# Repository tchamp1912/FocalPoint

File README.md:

# FocalPoint

FocalPoint is the attention router for your coding agents. It keeps Claude
Code, Codex CLI, and Cursor sessions visible in one native macOS dashboard,
then takes you straight to the agent that needs you next.

<p align="center"><em>One glance for every agent. One hotkey to jump back into the loop.</em></p>

## One hotkey takes you to the agent that needs you next

FocalPoint prioritizes errors and input requests across **Cursor, Claude Code,
and Codex**, then brings the corresponding window, tab, or pane forward—no
hunting through terminals.

Run several agents in parallel without becoming their human task scheduler.
When one needs approval, clarification, or help recovering from an error,
FocalPoint moves it to the front of the queue. Press the attention hotkey—or
the matching key on the macropad—to land where the work is waiting. Press it
again to move to the next agent that needs you.

Meanwhile, the menu-bar dashboard and desktop widget keep the whole operation
visible: which agents are thinking, which are running tools, which are done,
and how much context and quota each one has left.

## Install

FocalPoint currently requires **macOS 14 or newer on Apple Silicon**.

Install the prerequisites:

```sh
xcode-select --install
brew install rust jq
```

For precise managed-session focus and input routing, tmux is an optional
dependency:

```sh
brew install tmux
```

Then clone and run the installer:

```sh
git clone https://github.com/tchamp1912/FocalPoint.git
cd FocalPoint
./install.sh
```

The installer shows everything it will change and asks for confirmation. To
skip that prompt, run `./install.sh --yes`.

It will:

- build and install the `focalpointd` daemon, general `focalpoint` CLI, narrow
  native `fpctl-agent` orchestration client, and `focalpoint-mcp` coordination
  server;
- install and launch the native FocalPoint menu-bar app;
- configure a launchd user service so the daemon starts automatically;
- install the guarded `focalpoint-orchestrator` agent-control skill;
- install the Claude Code, Codex CLI, and Cursor adapters;
- install the managed-session launcher under `~/.config/focalpoint/` while
  preserving any existing FocalPoint tmux configuration;
- merge FocalPoint lifecycle hooks into each installed agent's user config,
  backing up those files before changing them;
- register the identity-bound coordination MCP server with Claude, Codex, and
  Cursor without overwriting same-name configurations; and
- preserve an existing `~/.config/focalpoint/config.toml`.

The app also includes a curated workflow catalog. **Start Workflow** and
**Workflow Editor** list bundled formations separately from installed packages.
Installing one asks for confirmation, copies its referenced agent types too,
and refuses any name collision rather than overwriting an existing package.

Restart any agent sessions that were already open so they load the new hooks.
The FocalPoint keyboard icon will appear in the macOS menu bar. Waiting/error
sessions are highlighted in the desktop widget without system notifications.
An orchestrator can set the daemon's attention order with `fpctl-agent`; the
app and attention key follow that same daemon-owned order.

With optional tmux support installed, start a managed agent using
`~/.config/focalpoint/focalpoint-run.sh claude` (or replace `claude` with
`codex` or `gemini`). See [the orchestrator guide](orchestrator/) for checkout usage and
layout options.

### Try it without the hardware

The app and all agent integrations work without a physical macropad. Install
in mock-device mode to exercise the complete software stack:

```sh
./install.sh --mock
```

### Verify the installation

```sh
focalpoint sessions       # live sessions and their assigned slots
focalpoint get-state      # aggregate agent state
```

`focalpoint ping` additionally checks for a connected hardware device, so it
is expected to fail with an app-only install unless the daemon is in mock mode.

## Features

### Attention routing, not notification noise

- Prioritize sessions that need intervention: errors first, then approval or
  input requests.
- Jump to the corresponding Cursor workspace, Claude terminal tab, or Codex
  working surface for that session.
- Cycle forward or backward through the attention queue with configurable
  global hotkeys.
- Let an orchestrator agent replace that queue with an explicit
  session order; the attention keys follow it without moving numbered slots.
- Launch a specific Claude or Codex model for a literal task in an exact, already-prepared
  directory. Environment/worktree setup remains the orchestrator's job.
- Read bounded normalized transcript tails and gracefully stop only the
  managed sessions associated with matching orchestrator task IDs.
- Use the same flow from numbered session keys on the physical macropad.
- Keep working while background agents think and run tools; FocalPoint tells
  you where your attention has the highest value.
- Permission requests get a two-second grace period, so Claude/Codex
  auto-approvals do not create false attention signals; only a request that
  remains blocked reaches `approval`; ordinary input requests use `waiting`.

### Every agent in one place

- Track concurrent Claude Code, Codex CLI, and Cursor sessions.
- Keep numbered slots stable while sessions change state, then compact them
  after a session ends or is removed.
- See the model, working directory, session name, current state, and elapsed
  time at a glance.
- Rename, reorder, focus, or end sessions directly from the app.

### Live stats and context pressure

- Display input/output tokens, tool calls, turns, subagents, and cost whenever
  the provider exposes them.
- Watch context-window consumption on a compact per-session gauge.
- Choose which stat badges appear from Settings.
- Set token and cost budget alerts for visual warning states.

### Status that is hard to miss

FocalPoint normalizes agent lifecycle events into six states:

| State | Meaning |
|---|---|
| `idle` | No active work |
| `thinking` | The model is reasoning or generating |
| `running` | A tool or command is executing |
| `waiting` | The agent needs ordinary user input |
| `approval` | A Claude Code permission decision needs attention |
| `done` | The current turn completed |
| `error` | Something failed and needs attention |

Those states drive the menu-bar attention badge, desktop widget, optional
keyboard backlight, and the RGB pattern assigned to each physical key.

### Account usage monitoring

- View Claude short-window and weekly quota periods.
- Read Codex plan limits through the local Codex app-server integration.
- Track Cursor API and Auto usage from the local Cursor sign-in.
- See utilization percentages and reset times without leaving your workflow.

Usage monitoring stays local and can be enabled or disabled per integration.

### Native macOS controls

- Compact menu-bar dashboard with a waiting/approval/error attention badge.
- Movable translucent desktop widget with the same live session data.
- Configurable global hotkeys for focusing sessions, accepting/rejecting,
  starting tasks, push-to-talk, and jumping through the attention queue.
- Quick actions that run in a session's working directory.
- Local history for completed sessions.

### Customizable hardware feedback

- Set a color, pattern, and animation period for every state.
- Use physical session keys to jump directly to the matching agent.
- Map the remaining keys, rotary dial, and joystick to your preferred agent
  workflow.
- Run the same action path through hotkeys when hardware is not connected.

## Supported integrations

| Integration | Live states | Session stats | Context gauge | Account usage |
|---|---:|---:|---:|---:|
| Claude Code | Yes | Yes | Yes | Yes |
| Codex CLI | Yes | Yes | Yes | Yes |
| Cursor | Yes | Yes | When available | Yes |
| Custom scripts and tools | Yes | Whatever you report | Optional | Optional |

Provider APIs expose different information, so a missing badge means that the
current integration or event did not report that value—not that the session
failed to register.

## Configure

Open **FocalPoint → Settings** from the menu-bar dashboard to configure:

- the desktop widget and menu-bar appearance;
- visible stat badges, budget alerts, and context-window fallback;
- Claude, Codex, and Cursor account-usage monitors;
- global hotkeys and attention-navigation order;
- per-state colors and LED animation patterns; and
- session history.

Low-level daemon actions and hardware mappings live in:

```text
~/.config/focalpoint/config.toml
```

## Update or uninstall

Pull the latest version and rerun the idempotent installer:

```sh
git pull
./install.sh
```

On every update, the installer also prunes obsolete files that a previous
FocalPoint release recorded as managed, removes managed binary copies from an
inactive install prefix, replaces the agent skill as an exact source snapshot,
and removes a duplicate FocalPoint app from the inactive Applications folder.
User configuration, session history, logs, and unrelated files are preserved.

To preview or perform a clean uninstall:

```sh
./uninstall.sh --dry-run
./uninstall.sh
```

## Build your own integration

Any tool that can run a shell command can publish state:

```sh
focalpoint set-state running \
  --session my-session \
  --kind my-agent \
  --label "Implement login flow" \
  --cwd "$PWD"
```

Adapters can attach optional telemetry with repeated `--meta key=value`
arguments. See [the adapter guide](adapters/) for complete examples.

## Developer documentation

The public README intentionally focuses on installing and using FocalPoint.
Contributor and implementation details live in:

- [CLAUDE.md](CLAUDE.md) — repository guidance and component map
- [PLAN.md](PLAN.md) — product, hardware, and roadmap notes
- [PROTOCOL.md](PROTOCOL.md) — daemon, adapter, and device protocol
- [app/README.md](app/) — macOS app behavior and development
- [adapters/README.md](adapters/) — provider and custom adapter development

FocalPoint is in active development. The app and mock-device stack are usable
today; the open-hardware macropad is still evolving.

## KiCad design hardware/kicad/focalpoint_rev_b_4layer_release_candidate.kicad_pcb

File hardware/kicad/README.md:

# FocalPoint KiCad Rev B

This directory is the persistent KiCad 10 workspace. The verified schematic is
the hierarchical root `focalpoint.kicad_sch` and its three child sheets; the current PCB is
`focalpoint_rev_b_4layer_release_candidate.kicad_pcb`. It is a fully routed four-layer
prototype candidate. Native KiCad DRC reports zero errors and zero unconnected
pads and zero violations. Thirty-seven intentionally modified embedded
footprints are locked to `FocalPoint.pretty` and independently audited. It is
not orderable until an independent review, purchased-part enclosure fit check,
and JLCPCB upload review are completed.

## Schematic hierarchy

- `focalpoint_power.kicad_sch`: USB power entry, charging, battery monitoring,
  3.3 V conversion, 5 V boost, and LED-rail switching.
- `focalpoint_signals.kicad_sch`: nRF52840 module, USB data protection,
  programming/debug, reset, and signal-conditioning parts.
- `focalpoint_peripherals.kicad_sch`: 13 keys and RGB LEDs, encoder, joystick,
  and capacitive-touch input.

Cross-sheet connections retain their reviewed global net names. This makes the
design a navigable file hierarchy without changing the electrical graph. The
locked pre-refactor capture is `focalpoint_flat_reference.kicad_sch`; running
`hierarchize_schematic.py` regenerates the hierarchy from that reference.
The generator also replaces the original stretched placeholder bodies with
conventional resistor, capacitor, inductor, TVS, switch, battery, and
power-flag notation. Each A2 child sheet uses a checked fixed-cell layout;
`hierarchical_schematic_layout_validation.txt` records zero overlapping block
pairs and confirms that every block remains inside the printable area.

The production stack-up, internal-plane policy, routing classes, and mandatory
USB impedance confirmation are defined in [PCB_FABRICATION.md](PCB_FABRICATION.md).

## Refresh the mechanical foundation

```sh
npx --yes ergogen@4.1.0 hardware/ergogen -o hardware/ergogen/output
hardware/kicad/refresh-from-ergogen.sh
```

The refresh script refuses to overwrite a board that has already gained
KiCad-owned electrical work. Once schematic capture or manual placement starts,
move Ergogen changes across deliberately instead of replacing the board.

Open `focalpoint_rev_b_4layer_release_candidate.kicad_pro` and
`focalpoint_rev_b_4layer_release_candidate.kicad_pcb` in KiCad 10. The
active 116 mm square design presents 16 input positions in a 4×4 layout: 13
direct-scan MX hot-swap keys plus the top-left EC11 encoder, top-right analog
joystick, and bottom-right capacitive touch input. Every mechanical key has an
independently addressable RGB LED.

## Functional blocks

1. `keys`: 13 direct GPIO key inputs, hot-swap sockets, and no matrix diodes.
2. `controls`: EC11 A/B/push and the selected joystick X/Y/push.
3. `mcu`: certified nRF52840 module, SWD, reset, and boot/recovery.
4. `usb`: USB-C USB 2.0 device, CC resistors, ESD, and data protection.
5. `power`: protected 1-cell LiPo, charger with power-path management, battery
   measurement, 3.3 V regulation, and switched/current-budgeted LED rail.
6. `rgb`: 13 SK6812 MINI-E LEDs, local bypassing, data conditioning, and test
   pads.

Do not assign unverified footprints for the radio, charger, battery connector,
or USB-C receptacle from a generic name. Pin them to an orderable manufacturer
part and verify the land pattern against its current datasheet first.

## Release-candidate build

After refilling zones, running native DRC, and saving its zero-violation report:

```sh
python3 hardware/kicad/build_release_candidate.py \
  --drc-report hardware/kicad/focalpoint_rev_b_4layer_release_DRC.rpt
```

The output is `release_candidate_rev_b_4layer/` plus Rev B candidate ZIP
archives. Read `RELEASE_STATUS.txt`; the builder requires a report containing
zero DRC violations, zero unconnected pads, and zero footprint errors.

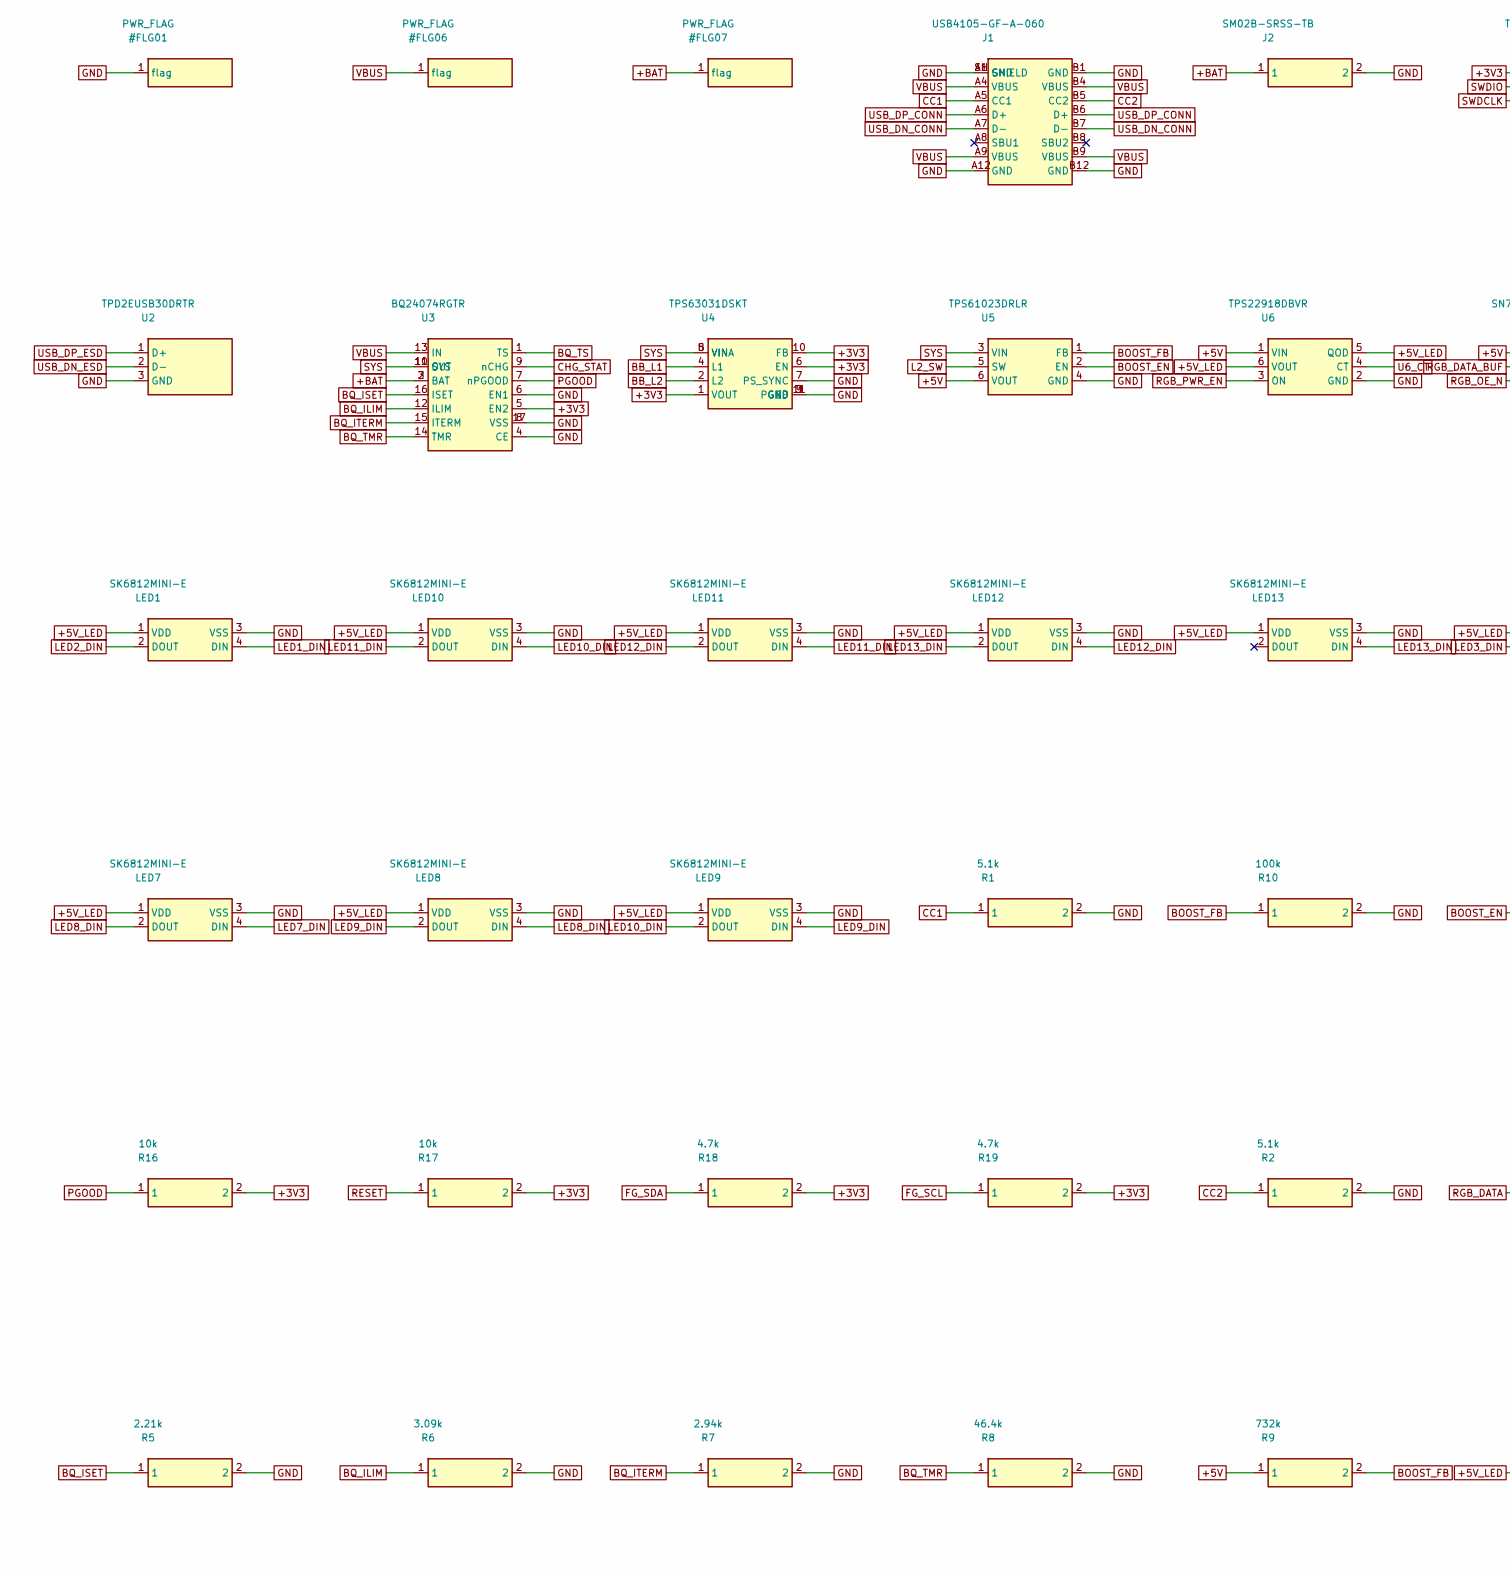
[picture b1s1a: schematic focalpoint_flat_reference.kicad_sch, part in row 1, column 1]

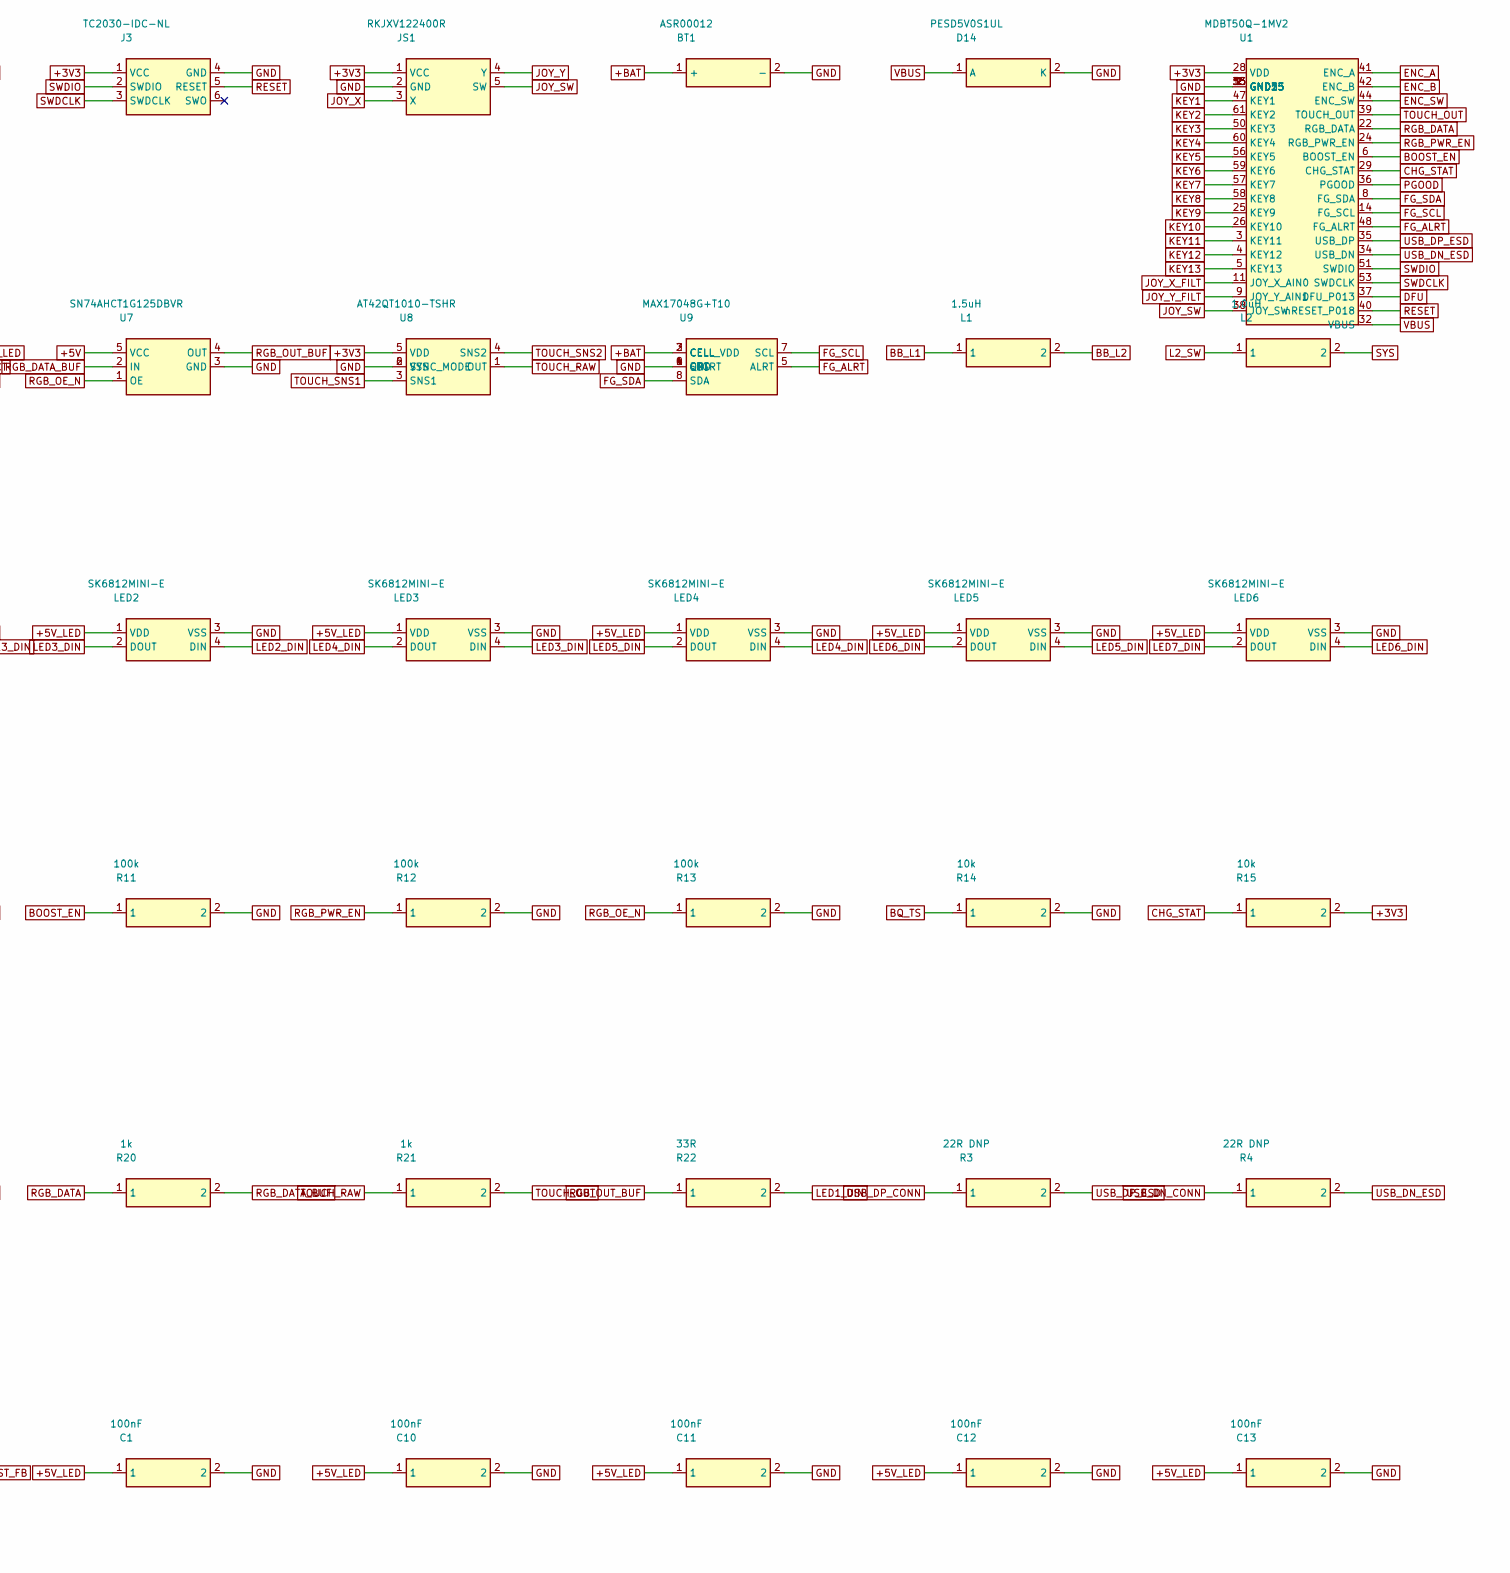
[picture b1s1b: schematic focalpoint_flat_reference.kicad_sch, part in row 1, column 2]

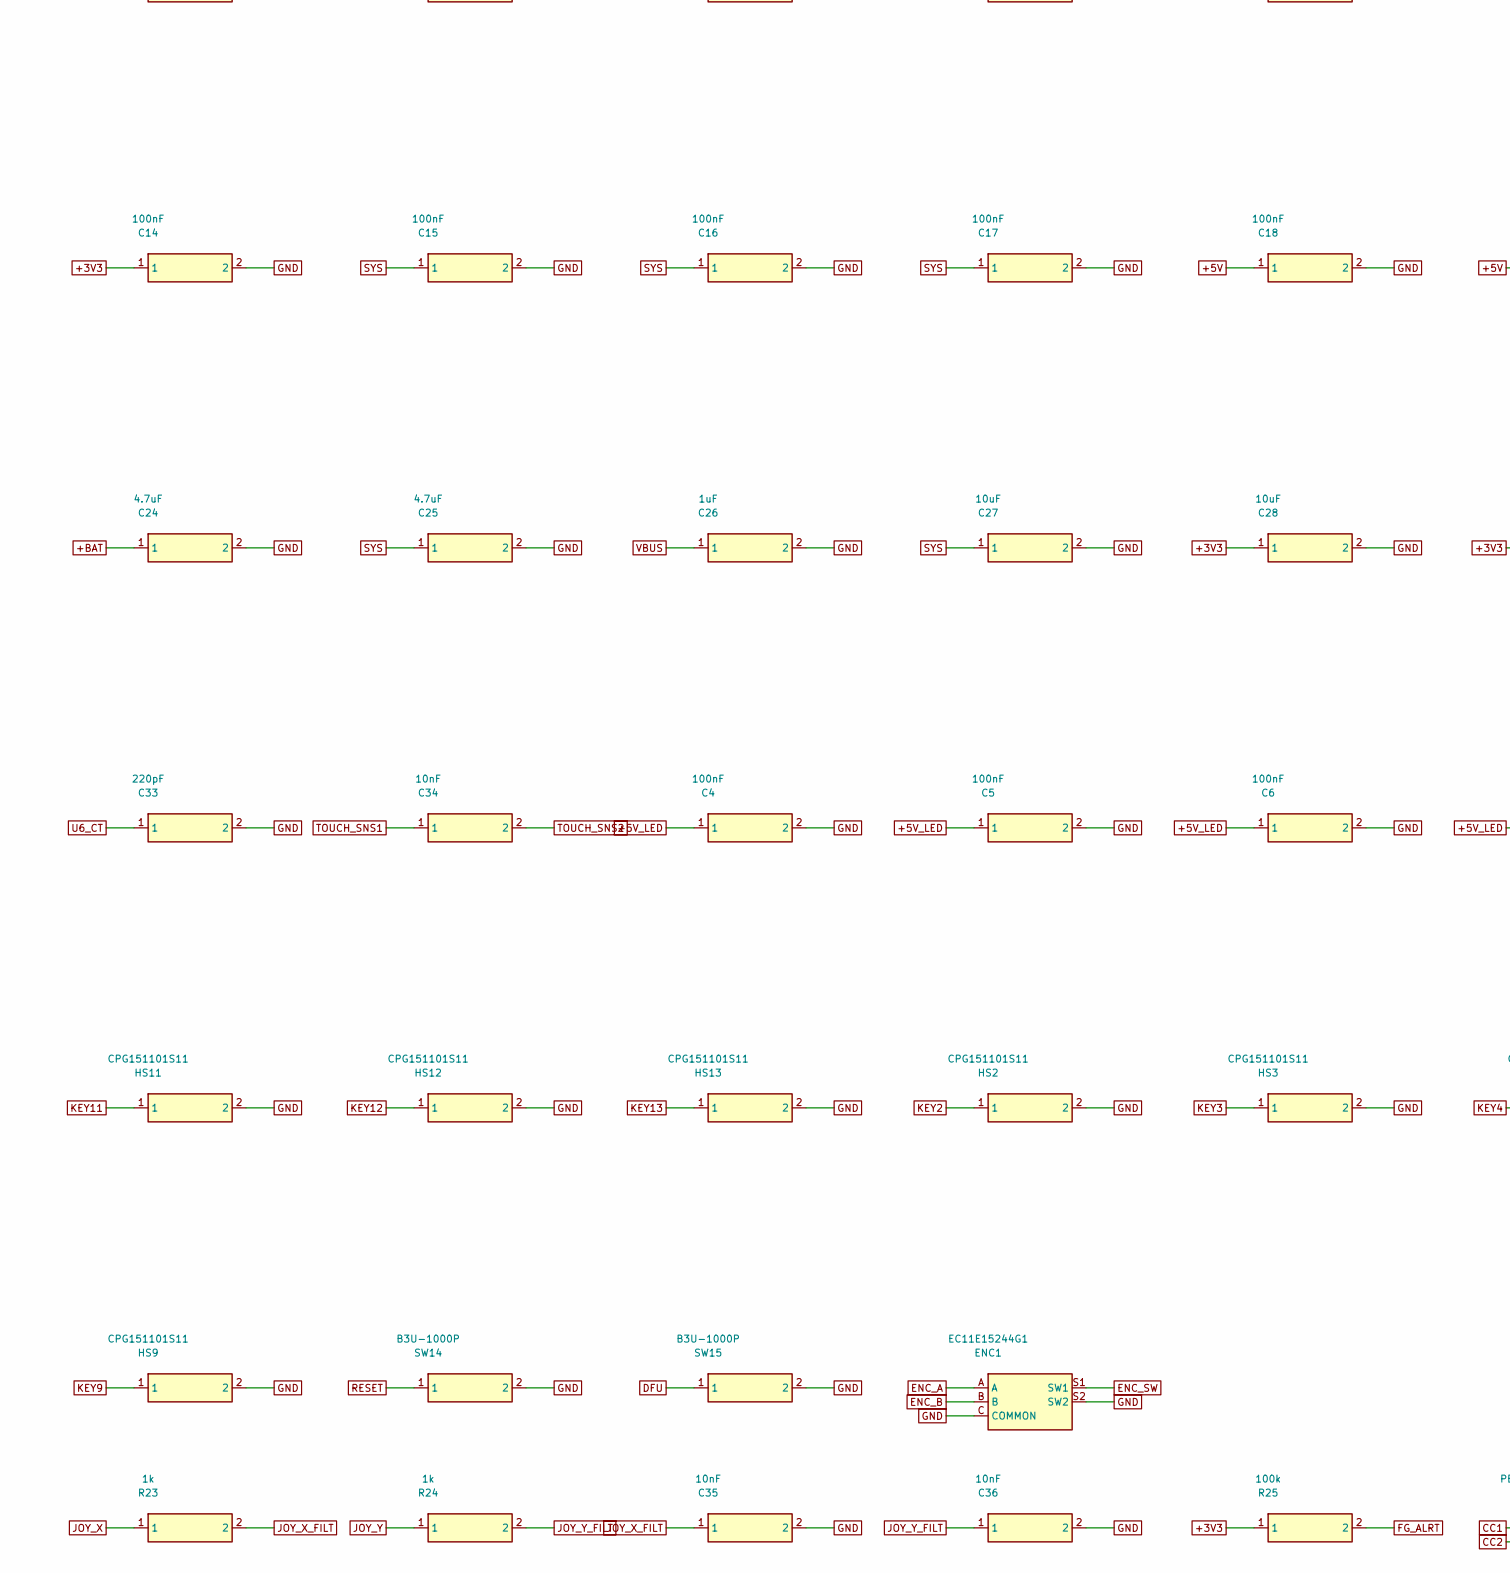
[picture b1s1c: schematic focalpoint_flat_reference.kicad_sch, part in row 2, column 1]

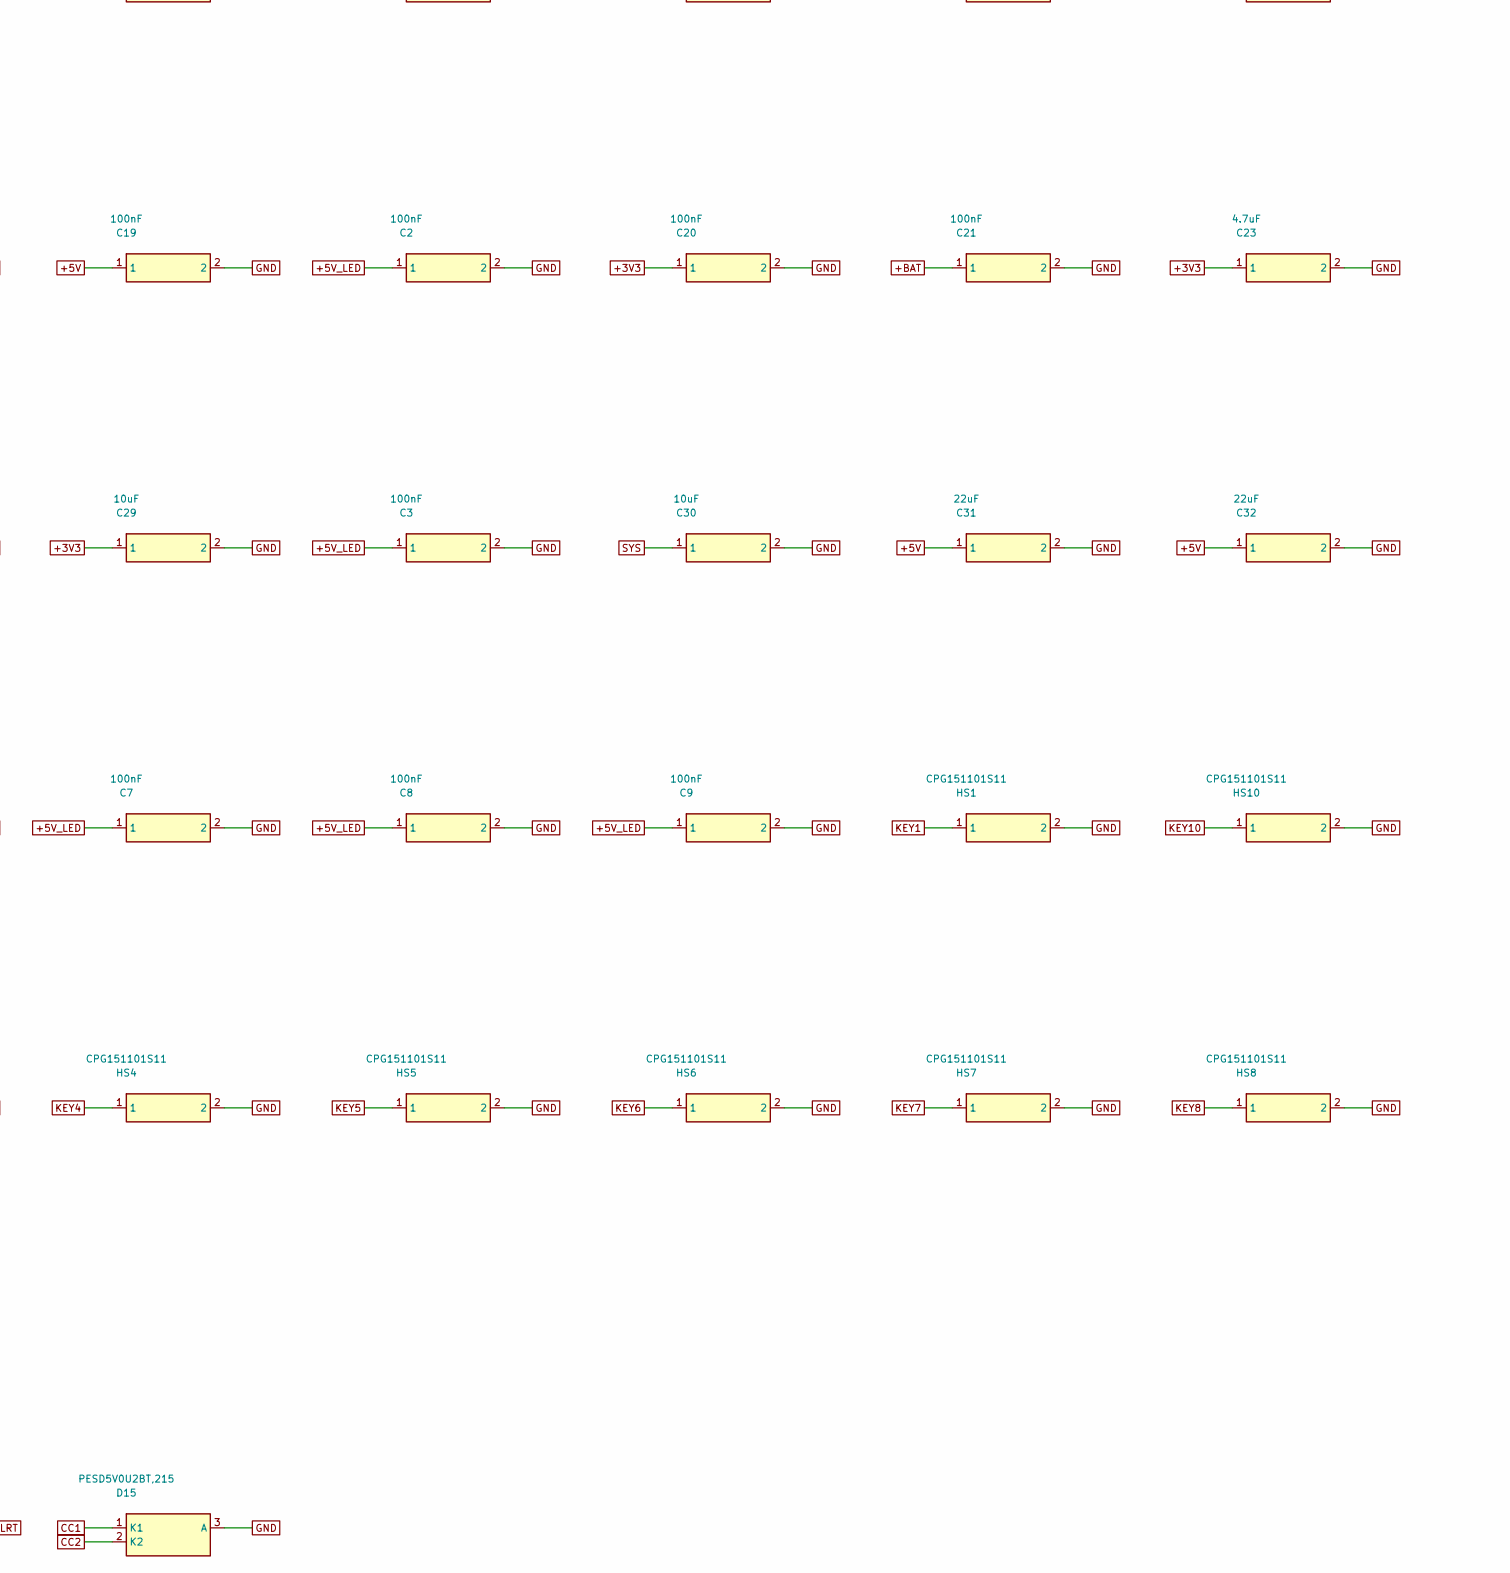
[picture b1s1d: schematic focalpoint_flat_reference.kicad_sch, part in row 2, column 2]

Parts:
BT1: ASR00012
C1, C2, C3, C4, C5, C6, C7, C8, C9, C10, C11, C12, C13, C14, C15, C16, C17, C18, C19, C20, C21: 100nF; C_0603_1608Metric
C23, C24, C25: 4.7uF; C_0603_1608Metric
C26: 1uF; C_0603_1608Metric
C27, C28, C29, C30: 10uF; C_0603_1608Metric
C31, C32: 22uF; C_0603_1608Metric
C33: 220pF; C_0603_1608Metric
C34, C35, C36: 10nF; C_0603_1608Metric
D14: PESD5V0S1UL; D_SOD-882
D15: PESD5V0U2BT,215; SOT-23
ENC1: EC11E15244G1; RotaryEncoder_Alps_EC11E-Switch_Vertical_H20mm
HS1, HS2, HS3, HS4, HS5, HS6, HS7, HS8, HS9, HS10, HS11, HS12, HS13: CPG151101S11; Kailh_CPG151101S11_Hotswap
J1: USB4105-GF-A-060; USB_C_Receptacle_GCT_USB4105-xx-A_16P_TopMnt_Horizontal
J2: SM02B-SRSS-TB; JST_SH_SM02B-SRSS-TB_1x02-1MP_P1.00mm_Horizontal
J3: TC2030-IDC-NL; Tag-Connect_TC2030-IDC-NL_2x03_P1.27mm_Vertical
JS1: RKJXV122400R; Alps_RKJXV122400R
L1: 1.5uH; L_Sunlord_SWPA3015S
L2: 1.0uH; L_Sunlord_MWSA0402S
LED1, LED2, LED3, LED4, LED5, LED6, LED7, LED8, LED9, LED10, LED11, LED12, LED13: SK6812MINI-E; LED_SK6812MINI-E_3.2x2.8mm_P1.5mm_ReverseMount
R1, R2: 5.1k; R_0603_1608Metric
R3, R4: 22R DNP; R_0603_1608Metric
R5: 2.21k; R_0603_1608Metric
R6: 3.09k; R_0603_1608Metric
R7: 2.94k; R_0603_1608Metric
R8: 46.4k; R_0603_1608Metric
R9: 732k; R_0603_1608Metric
R10, R11, R12, R13, R25: 100k; R_0603_1608Metric
R14, R15, R16, R17: 10k; R_0603_1608Metric
R18, R19: 4.7k; R_0603_1608Metric
R20, R21, R23, R24: 1k; R_0603_1608Metric
R22: 33R; R_0603_1608Metric
SW14, SW15: B3U-1000P; SW_SPST_B3U-1000P
U1: MDBT50Q-1MV2; Raytac_MDBT50Q
U2: TPD2EUSB30DRTR; Texas_DRT-3
U3: BQ24074RGTR; VQFN-16-1EP_3x3mm_P0.5mm_EP1.68x1.68mm_ThermalVias
U4: TPS63031DSKT; WSON-10-1EP_2.5x2.5mm_P0.5mm_EP1.2x2mm_ThermalVias
U5: TPS61023DRLR; SOT-563
U6: TPS22918DBVR; SOT-23-6
U7: SN74AHCT1G125DBVR; SOT-23-5
U8: AT42QT1010-TSHR; SOT-23-6
U9: MAX17048G+T10; TDFN-8-1EP_2x2mm_P0.5mm_EP0.8x1.2mm

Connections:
+3V3: C14.1, C20.1, C23.1, C28.1, C29.1, J3.1 (VCC), JS1.1 (VCC), R15.2, R16.2, R17.2, R18.2, R19.2, R25.1, U1.28 (VDD), U3.5 (EN2), U4.1 (VOUT), U4.6 (EN), U4.10 (FB), U8.5 (VDD)
+5V: C18.1, C19.1, C31.1, C32.1, R9.1, U5.6 (VOUT), U6.1 (VIN), U7.5 (VCC)
+5V_LED: C1.1, C2.1, C3.1, C4.1, C5.1, C6.1, C7.1, C8.1, C9.1, C10.1, C11.1, C12.1, C13.1, LED1.1 (VDD), LED2.1 (VDD), LED3.1 (VDD), LED4.1 (VDD), LED5.1 (VDD), LED6.1 (VDD), LED7.1 (VDD), LED8.1 (VDD), LED9.1 (VDD), LED10.1 (VDD), LED11.1 (VDD), LED12.1 (VDD), LED13.1 (VDD), U6.5 (QOD), U6.6 (VOUT)
+BAT: BT1.1 (+), C21.1, C24.1, J2.1, U3.2 (BAT), U3.3 (BAT), U9.2 (CELL), U9.3 (CELL_VDD)
BB_L1: L1.1, U4.4 (L1)
BB_L2: L1.2, U4.2 (L2)
BOOST_EN: R11.1, U1.6 (BOOST_EN), U5.2 (EN)
BOOST_FB: R9.2, R10.1, U5.1 (FB)
BQ_ILIM: R6.1, U3.12 (ILIM)
BQ_ISET: R5.1, U3.16 (ISET)
BQ_ITERM: R7.1, U3.15 (ITERM)
BQ_TMR: R8.1, U3.14 (TMR)
BQ_TS: R14.1, U3.1 (TS)
CC1: D15.1 (K1), J1.A5 (CC1), R1.1
CC2: D15.2 (K2), J1.B5 (CC2), R2.1
CHG_STAT: R15.1, U1.29 (CHG_STAT), U3.9 (nCHG)
DFU: SW15.1, U1.37 (DFU_P013)
ENC_A: ENC1.A, U1.41 (ENC_A)
ENC_B: ENC1.B, U1.42 (ENC_B)
ENC_SW: ENC1.S1 (SW1), U1.44 (ENC_SW)
FG_ALRT: R25.2, U1.48 (FG_ALRT), U9.5 (ALRT)
FG_SCL: R19.1, U1.14 (FG_SCL), U9.7 (SCL)
FG_SDA: R18.1, U1.8 (FG_SDA), U9.8 (SDA)
GND: BT1.2 (-), C1.2, C2.2, C3.2, C4.2, C5.2, C6.2, C7.2, C8.2, C9.2, C10.2, C11.2, C12.2, C13.2, C14.2, C15.2, C16.2, C17.2, C18.2, C19.2, C20.2, C21.2, C23.2, C24.2, C25.2, C26.2, C27.2, C28.2, C29.2, C30.2, C31.2, C32.2, C33.2, C35.2, C36.2, D14.2 (K), D15.3 (A), ENC1.C (COMMON), ENC1.S2 (SW2), HS1.2, HS2.2, HS3.2, HS4.2, HS5.2, HS6.2, HS7.2, HS8.2, HS9.2, HS10.2, HS11.2, HS12.2, HS13.2, J1.A1 (GND), J1.A12 (GND), J1.B1 (GND), J1.B12 (GND), J1.SH (SHIELD), J2.2, J3.4 (GND), JS1.2 (GND), LED1.3 (VSS), LED2.3 (VSS), LED3.3 (VSS), LED4.3 (VSS), LED5.3 (VSS), LED6.3 (VSS), LED7.3 (VSS), LED8.3 (VSS), LED9.3 (VSS), LED10.3 (VSS), LED11.3 (VSS), LED12.3 (VSS), LED13.3 (VSS), R1.2, R2.2, R5.2, R6.2, R7.2, R8.2, R10.2, R11.2, R12.2, R13.2, R14.2, SW14.2, SW15.2, U1.1 (GND), U1.2 (GND2), U1.15 (GND15), U1.33 (GND33), U1.55 (GND55), U2.3 (GND), U3.4 (CE), U3.6 (EN1), U3.8 (VSS), U3.17 (VSS), U4.3 (PGND), U4.7 (PS_SYNC), U4.9 (GND), U4.11 (EP), U5.4 (GND), U6.2 (GND), U7.3 (GND), U8.2 (VSS), U8.6 (SYNC_MODE), U9.1 (CTG), U9.4 (GND), U9.6 (QSTRT), U9.9 (EP)
JOY_SW: JS1.5 (SW), U1.38 (JOY_SW)
JOY_X: JS1.3 (X), R23.1
JOY_X_FILT: C35.1, R23.2, U1.11 (JOY_X_AIN0)
JOY_Y: JS1.4 (Y), R24.1
JOY_Y_FILT: C36.1, R24.2, U1.9 (JOY_Y_AIN1)
KEY1: HS1.1, U1.47 (KEY1)
KEY2: HS2.1, U1.61 (KEY2)
KEY3: HS3.1, U1.50 (KEY3)
KEY4: HS4.1, U1.60 (KEY4)
KEY5: HS5.1, U1.56 (KEY5)
KEY6: HS6.1, U1.59 (KEY6)
KEY7: HS7.1, U1.57 (KEY7)
KEY8: HS8.1, U1.58 (KEY8)
KEY9: HS9.1, U1.25 (KEY9)
KEY10: HS10.1, U1.26 (KEY10)
KEY11: HS11.1, U1.3 (KEY11)
KEY12: HS12.1, U1.4 (KEY12)
KEY13: HS13.1, U1.5 (KEY13)
L2_SW: L2.1, U5.5 (SW)
LED1_DIN: LED1.4 (DIN), R22.2
LED2_DIN: LED1.2 (DOUT), LED2.4 (DIN)
LED3_DIN: LED2.2 (DOUT), LED3.4 (DIN)
LED4_DIN: LED3.2 (DOUT), LED4.4 (DIN)
LED5_DIN: LED4.2 (DOUT), LED5.4 (DIN)
LED6_DIN: LED5.2 (DOUT), LED6.4 (DIN)
LED7_DIN: LED6.2 (DOUT), LED7.4 (DIN)
LED8_DIN: LED7.2 (DOUT), LED8.4 (DIN)
LED9_DIN: LED8.2 (DOUT), LED9.4 (DIN)
LED10_DIN: LED9.2 (DOUT), LED10.4 (DIN)
LED11_DIN: LED10.2 (DOUT), LED11.4 (DIN)
LED12_DIN: LED11.2 (DOUT), LED12.4 (DIN)
LED13_DIN: LED12.2 (DOUT), LED13.4 (DIN)
PGOOD: R16.1, U1.36 (PGOOD), U3.7 (nPGOOD)
RESET: J3.5 (RESET), R17.1, SW14.1, U1.40 (nRESET_P018)
RGB_DATA: R20.1, U1.22 (RGB_DATA)
RGB_DATA_BUF: R20.2, U7.2 (IN)
RGB_OE_N: R13.1, U7.1 (OE)
RGB_OUT_BUF: R22.1, U7.4 (OUT)
RGB_PWR_EN: R12.1, U1.24 (RGB_PWR_EN), U6.3 (ON)
SWDCLK: J3.3 (SWDCLK), U1.53 (SWDCLK)
SWDIO: J3.2 (SWDIO), U1.51 (SWDIO)
SYS: C15.1, C16.1, C17.1, C25.1, C27.1, C30.1, L2.2, U3.10 (SYS), U3.11 (OUT), U4.5 (VIN), U4.8 (VINA), U5.3 (VIN)
TOUCH_OUT: R21.2, U1.39 (TOUCH_OUT)
TOUCH_RAW: R21.1, U8.1 (OUT)
TOUCH_SNS1: C34.1, U8.3 (SNS1)
TOUCH_SNS2: C34.2, U8.4 (SNS2)
U6_CT: C33.1, U6.4 (CT)
USB_DN_CONN: J1.A7 (D-), J1.B7 (D-), R4.1
USB_DN_ESD: R4.2, U1.34 (USB_DN), U2.2 (D-)
USB_DP_CONN: J1.A6 (D+), J1.B6 (D+), R3.1
USB_DP_ESD: R3.2, U1.35 (USB_DP), U2.1 (D+)
VBUS: C26.1, D14.1 (A), J1.A4 (VBUS), J1.A9 (VBUS), J1.B4 (VBUS), J1.B9 (VBUS), U1.32 (VBUS), U3.13 (IN)

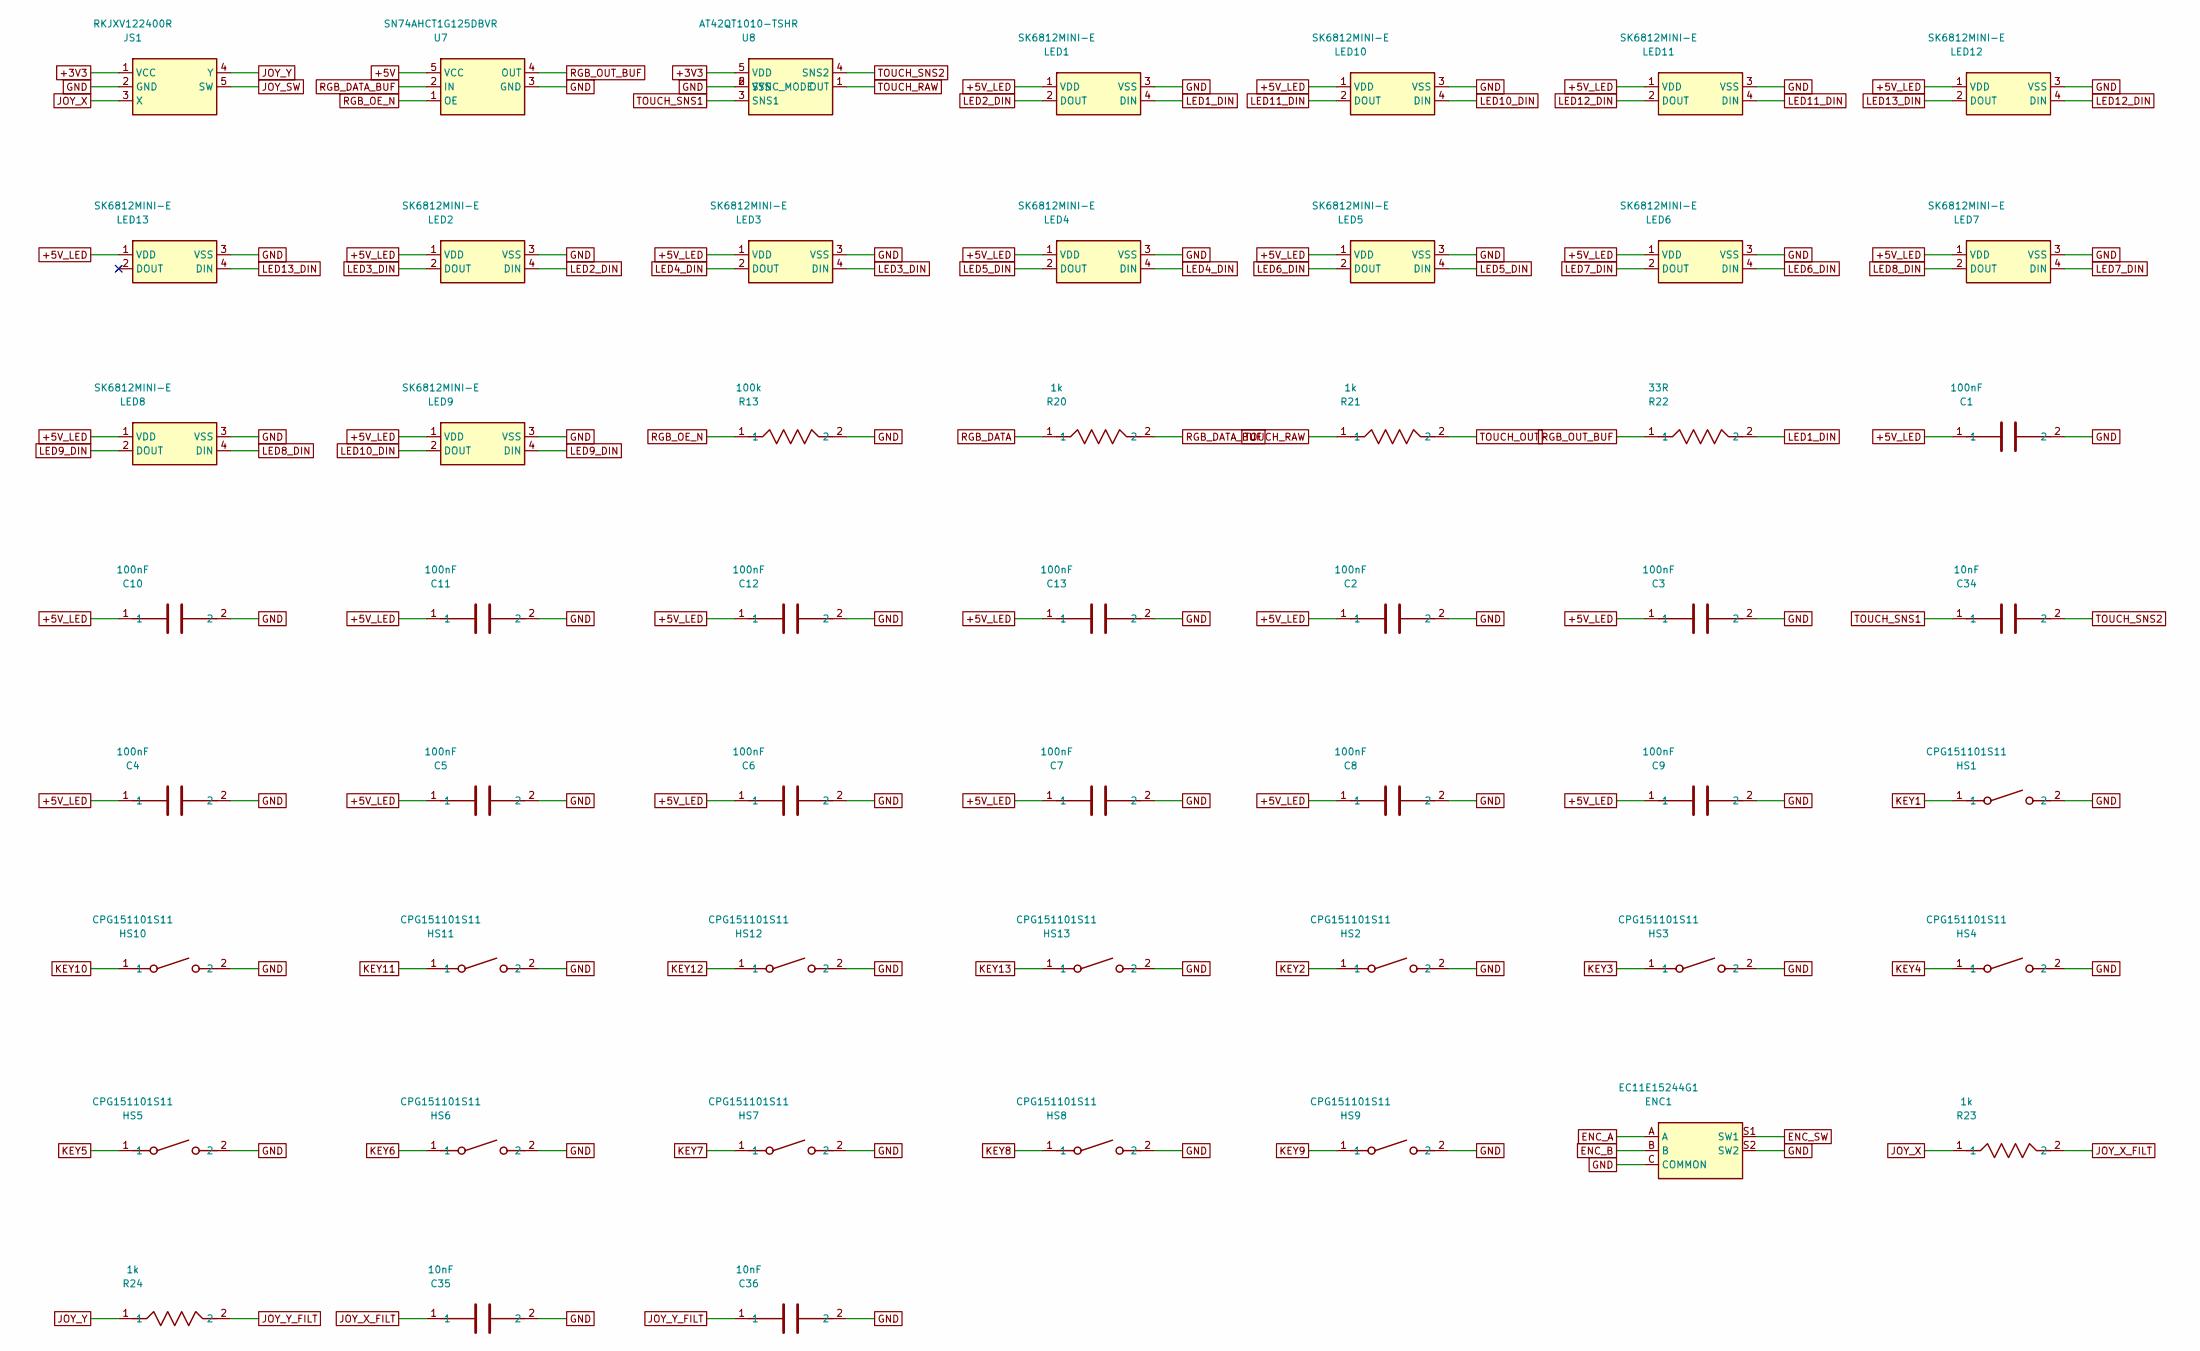
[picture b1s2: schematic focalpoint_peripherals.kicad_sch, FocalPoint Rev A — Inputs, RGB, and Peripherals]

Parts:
C1, C2, C3, C4, C5, C6, C7, C8, C9, C10, C11, C12, C13: 100nF; C_0603_1608Metric
C34, C35, C36: 10nF; C_0603_1608Metric
ENC1: EC11E15244G1; RotaryEncoder_Alps_EC11E-Switch_Vertical_H20mm
HS1, HS2, HS3, HS4, HS5, HS6, HS7, HS8, HS9, HS10, HS11, HS12, HS13: CPG151101S11; Kailh_CPG151101S11_Hotswap
JS1: RKJXV122400R; Alps_RKJXV122400R
LED1, LED2, LED3, LED4, LED5, LED6, LED7, LED8, LED9, LED10, LED11, LED12, LED13: SK6812MINI-E; LED_SK6812MINI-E_3.2x2.8mm_P1.5mm_ReverseMount
R13: 100k; R_0603_1608Metric
R20, R21, R23, R24: 1k; R_0603_1608Metric
R22: 33R; R_0603_1608Metric
U7: SN74AHCT1G125DBVR; SOT-23-5
U8: AT42QT1010-TSHR; SOT-23-6

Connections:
+3V3: JS1.1 (VCC), U8.5 (VDD); also elsewhere on the board
+5V: U7.5 (VCC); also elsewhere on the board
+5V_LED: C1.1, C2.1, C3.1, C4.1, C5.1, C6.1, C7.1, C8.1, C9.1, C10.1, C11.1, C12.1, C13.1, LED1.1 (VDD), LED2.1 (VDD), LED3.1 (VDD), LED4.1 (VDD), LED5.1 (VDD), LED6.1 (VDD), LED7.1 (VDD), LED8.1 (VDD), LED9.1 (VDD), LED10.1 (VDD), LED11.1 (VDD), LED12.1 (VDD), LED13.1 (VDD); also elsewhere on the board
ENC_A: ENC1.A; also elsewhere on the board
ENC_B: ENC1.B; also elsewhere on the board
ENC_SW: ENC1.S1 (SW1); also elsewhere on the board
GND: C1.2, C2.2, C3.2, C4.2, C5.2, C6.2, C7.2, C8.2, C9.2, C10.2, C11.2, C12.2, C13.2, C35.2, C36.2, ENC1.C (COMMON), ENC1.S2 (SW2), HS1.2, HS2.2, HS3.2, HS4.2, HS5.2, HS6.2, HS7.2, HS8.2, HS9.2, HS10.2, HS11.2, HS12.2, HS13.2, JS1.2 (GND), LED1.3 (VSS), LED2.3 (VSS), LED3.3 (VSS), LED4.3 (VSS), LED5.3 (VSS), LED6.3 (VSS), LED7.3 (VSS), LED8.3 (VSS), LED9.3 (VSS), LED10.3 (VSS), LED11.3 (VSS), LED12.3 (VSS), LED13.3 (VSS), R13.2, U7.3 (GND), U8.2 (VSS), U8.6 (SYNC_MODE); also elsewhere on the board
JOY_SW: JS1.5 (SW); also elsewhere on the board
JOY_X: JS1.3 (X), R23.1
JOY_X_FILT: C35.1, R23.2; also elsewhere on the board
JOY_Y: JS1.4 (Y), R24.1
JOY_Y_FILT: C36.1, R24.2; also elsewhere on the board
KEY1: HS1.1; also elsewhere on the board
KEY2: HS2.1; also elsewhere on the board
KEY3: HS3.1; also elsewhere on the board
KEY4: HS4.1; also elsewhere on the board
KEY5: HS5.1; also elsewhere on the board
KEY6: HS6.1; also elsewhere on the board
KEY7: HS7.1; also elsewhere on the board
KEY8: HS8.1; also elsewhere on the board
KEY9: HS9.1; also elsewhere on the board
KEY10: HS10.1; also elsewhere on the board
KEY11: HS11.1; also elsewhere on the board
KEY12: HS12.1; also elsewhere on the board
KEY13: HS13.1; also elsewhere on the board
LED1_DIN: LED1.4 (DIN), R22.2
LED2_DIN: LED1.2 (DOUT), LED2.4 (DIN)
LED3_DIN: LED2.2 (DOUT), LED3.4 (DIN)
LED4_DIN: LED3.2 (DOUT), LED4.4 (DIN)
LED5_DIN: LED4.2 (DOUT), LED5.4 (DIN)
LED6_DIN: LED5.2 (DOUT), LED6.4 (DIN)
LED7_DIN: LED6.2 (DOUT), LED7.4 (DIN)
LED8_DIN: LED7.2 (DOUT), LED8.4 (DIN)
LED9_DIN: LED8.2 (DOUT), LED9.4 (DIN)
LED10_DIN: LED9.2 (DOUT), LED10.4 (DIN)
LED11_DIN: LED10.2 (DOUT), LED11.4 (DIN)
LED12_DIN: LED11.2 (DOUT), LED12.4 (DIN)
LED13_DIN: LED12.2 (DOUT), LED13.4 (DIN)
RGB_DATA: R20.1; also elsewhere on the board
RGB_DATA_BUF: R20.2, U7.2 (IN)
RGB_OE_N: R13.1, U7.1 (OE)
RGB_OUT_BUF: R22.1, U7.4 (OUT)
TOUCH_OUT: R21.2; also elsewhere on the board
TOUCH_RAW: R21.1, U8.1 (OUT)
TOUCH_SNS1: C34.1, U8.3 (SNS1)
TOUCH_SNS2: C34.2, U8.4 (SNS2)
